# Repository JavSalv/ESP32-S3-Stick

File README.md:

# ESP32-S3 Stick

> Breadboard-friendly ESP32-S3 module with onboard RTC, LiPo battery charger, and USB-C — designed for low-power and deep-sleep applications.

---

## Overview

The ESP32-S3 Stick is a compact development module built around the **ESP32-S3-WROOM-1** that fits standard 830-point breadboards leaving room on both sides of the module.
It combines a complete power path (USB-C input, LiPo charging, and a synchronous buck converter) with an ultra-low-power RTC clock, making it well suited for prototyping battery-operated IoT nodes, data loggers, and any application that relies on deep sleep.

---

## Features

### Microcontroller
- **ESP32-S3-WROOM-1-N16R2**: Dual-core Xtensa LX7 @ up to 240 MHz, 16 MB Flash, 2 MB PSRAM
- All GPIOs broken out to the standard 22-pin headers.

### Power
- **USB-C input** (USB 2.0, 16-pin receptacle) with correct CC pull-downs for UFP/sink detection
- **MCP73831** single-cell LiPo/Li-Ion charger with 100 mA charge current (configurable via R_PROG)
- **TPS629210** synchronous buck converter for 3.3V output up to 1A.
- **P-channel MOSFET load-sharing** (DMP2045U-7) seamless switchover between USB and battery with low dropout penalty.
- **USBLC6-2SC6** TVS diode array for USB ESD protection.

### RTC
- **RV-3028-C7** — ultra-low-power RTC (40 nA), ±1 ppm accuracy, I²C interface on IO13 (SCL) / IO14 (SDA)

### Connectivity & I/O
- **USB-C** - USB 2.0 FS data lines connected directly to ESP32-S3 USB transceiver (USB_D+ / USB_D−)
- **UART0** (TXD0 / RXD0) broken out for programming and debug
- **2 × 22-pin headers** 2.54 mm pitch, breadboard-compatible

### User Interface
- **RST button**: Reset the controller
- **BOOT button**: Enters download mode when held during reset
- **3 × status LEDs**: Charge status, power status and one user LED connected to GPIO48

---

## Pin Map

The Pin Map is similar to other ESP32-S3 modules like the ESP32-S3-DevKitC-1 or cheaper AliExpress clones.

> **Note:** IO0 is the BOOT strapping pin — avoid driving it LOW at power-on unless entering download mode. IO45 and IO46 are also strapping pins; check the ESP32-S3 datasheet before using them as outputs.

### LiPo Battery

Connect a single-cell LiPo or Li-Ion battery (3.7 V nominal) to the battery connector (JST PH 2-pin 2mm pitch connector). The MCP73831 charges the battery at 100mA.

## License

Hardware design files are open source. See [LICENSE](LICENSE) for details.

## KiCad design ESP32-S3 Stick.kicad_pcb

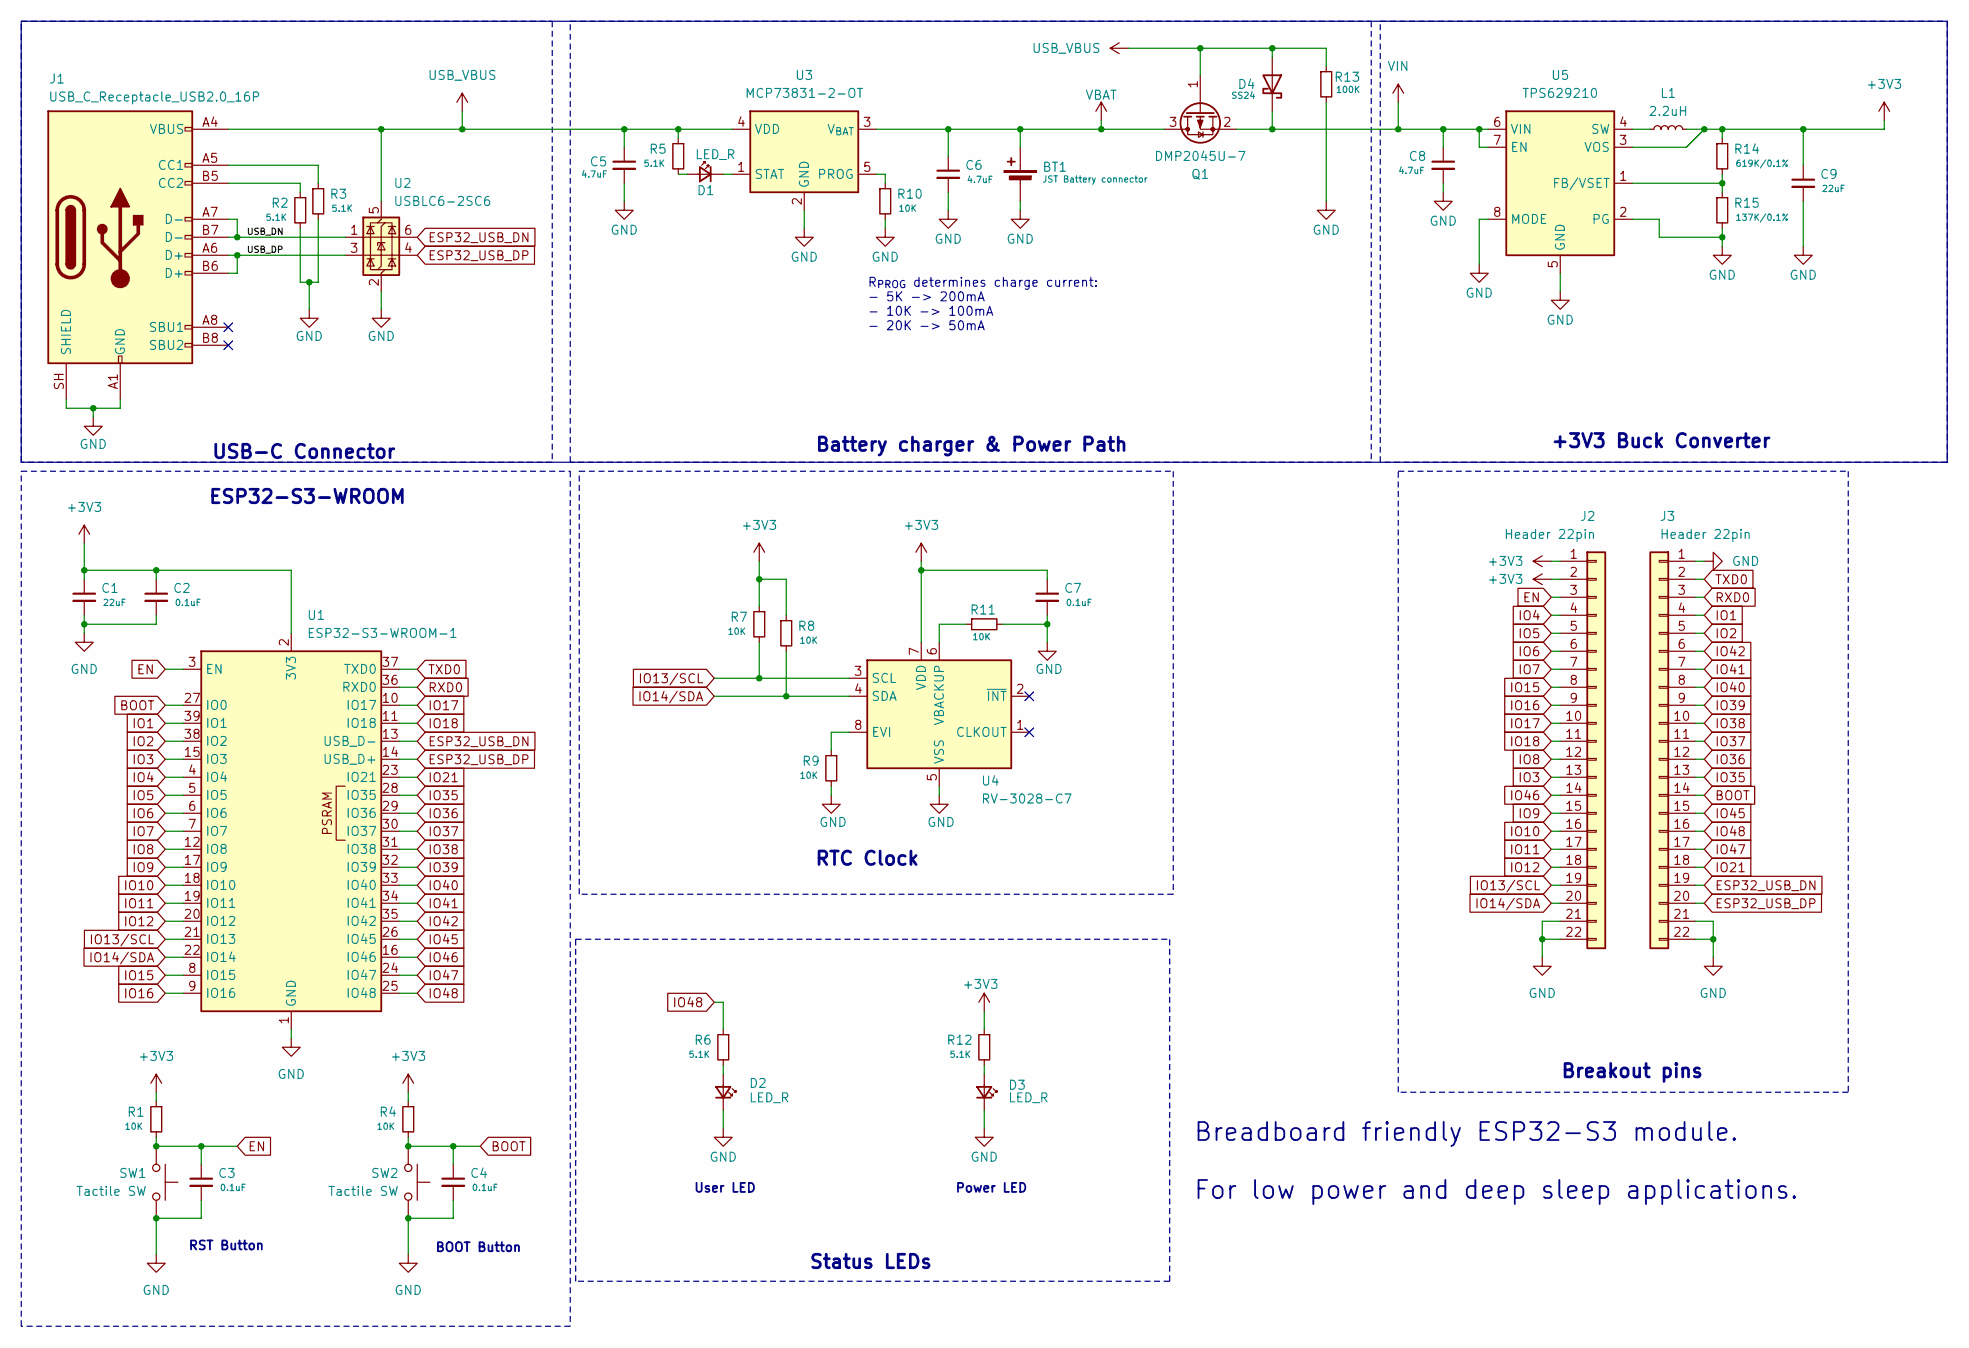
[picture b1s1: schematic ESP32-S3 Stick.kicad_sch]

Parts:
BT1: JST Battery connector; CONN-TH_B2B-PH-K-S; digikey# 455-1704-ND
C1, C9: 22uF; C_0603_1608Metric; digikey# 1276-1274-1-ND
C2, C3, C4, C7: 0.1uF; C_0603_1608Metric; digikey# 1276-1000-1-ND
C5, C6, C8: 4.7uF; C_0603_1608Metric; digikey# 1276-1900-1-ND
D1, D2, D3: LED_R; LED_0603_1608Metric; digikey# 160-1830-1-ND
D4: SS24; D_SOD-123F; digikey# 1801-SS24LWCT-ND
J1: USB_C_Receptacle_USB2.0_16P; USB_C_Receptacle_GCT_USB4105-xx-A_16P_TopMnt_Horizontal; digikey# 2073-USB4215-03-ACT-ND
J2, J3: Header 22pin; PinHeader_1x22_P2.54mm_Vertical; lcsc# C41375941
L1: 2.2uH; L_1008_2520Metric; digikey# 490-DFE252012PD-2R2M=P2CT-ND
Q1: DMP2045U-7; SOT-23; lcsc# C459541
R1, R4, R7, R8, R9, R10, R11: 10K; R_0603_1608Metric; digikey# YAG1236CT-ND
R2, R3, R5, R6, R12: 5.1K; R_0603_1608Metric; digikey# YAG1696CT-ND
R13: 100K; R_0603_1608Metric; digikey# 311-100KGRCT-ND
R14: 619K/0.1%; R_0603_1608Metric; digikey# MCT0603MD6193BP500
R15: 137K/0.1%; R_0603_1608Metric; digikey# ERA-3AEB1373V
SW1, SW2: Tactile SW; SW-SMD_L3.9-W3.0-P4.45; digikey# 4809-SKRKAEE020CT-ND
U1: ESP32-S3-WROOM-1; digikey# 5407-ESP32-S3-WROOM-1-N16R2CT-ND
U2: USBLC6-2SC6; SOT-23-6; digikey# 5399-USBLC6-2SC6CT-ND
U3: MCP73831-2-OT; SOT-23-5; digikey# MCP73831T-2ACI/OTCT-ND
U4: RV-3028-C7; MicroCrystal_C7_SON-8_1.5x3.2mm_P0.9mm; lcsc# C3019759
U5: TPS629210; SOT-583-8; digikey# 296-TPS629210DRLRCT-ND

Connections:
+3V3: C1.1, C2.1, C7.1, C9.1, J2.1, J2.2, L1.2, R1.1, R4.1, R7.1, R8.1, R12.1, R14.1, U1.2 (3V3), U4.7 (VDD), U5.3 (VOS)
/USB_DN: J1.A7 (D-), J1.B7 (D-), U2.1 (I/O1)
/USB_DP: J1.A6 (D+), J1.B6 (D+), U2.3 (I/O2)
BOOT: C4.1, J3.14, R4.2, SW2.2, U1.27 (IO0)
EN: C3.1, J2.3, R1.2, SW1.2, U1.3 (EN)
ESP32_USB_DN: J3.19, U1.13 (USB_D-), U2.6 (I/O1)
ESP32_USB_DP: J3.20, U1.14 (USB_D+), U2.4 (I/O2)
GND: BT1.2 (-), C1.2, C2.2, C3.2, C4.2, C5.2, C6.2, C7.2, C8.2, C9.2, D2.1 (K), D3.1 (K), J1.A1 (GND), J1.A12 (GND), J1.B1 (GND), J1.B12 (GND), J1.SH (SHIELD), J2.21, J2.22, J3.1, J3.21, J3.22, R2.2, R3.2, R9.2, R10.2, R11.2, R13.2, R15.2, SW1.1, SW2.1, U1.1 (GND), U1.40 (GND), U1.41 (GND), U2.2 (GND), U3.2 (GND), U4.5 (VSS), U5.2 (PG), U5.5 (GND), U5.8 (MODE)
IO1: J3.4, U1.39 (IO1)
IO2: J3.5, U1.38 (IO2)
IO3: J2.13, U1.15 (IO3)
IO4: J2.4, U1.4 (IO4)
IO5: J2.5, U1.5 (IO5)
IO6: J2.6, U1.6 (IO6)
IO7: J2.7, U1.7 (IO7)
IO8: J2.12, U1.12 (IO8)
IO9: J2.15, U1.17 (IO9)
IO10: J2.16, U1.18 (IO10)
IO11: J2.17, U1.19 (IO11)
IO12: J2.18, U1.20 (IO12)
IO13/SCL: J2.19, R7.2, U1.21 (IO13), U4.3 (SCL)
IO14/SDA: J2.20, R8.2, U1.22 (IO14), U4.4 (SDA)
IO15: J2.8, U1.8 (IO15)
IO16: J2.9, U1.9 (IO16)
IO17: J2.10, U1.10 (IO17)
IO18: J2.11, U1.11 (IO18)
IO21: J3.18, U1.23 (IO21)
IO35: J3.13, U1.28 (IO35)
IO36: J3.12, U1.29 (IO36)
IO37: J3.11, U1.30 (IO37)
IO38: J3.10, U1.31 (IO38)
IO39: J3.9, U1.32 (IO39)
IO40: J3.8, U1.33 (IO40)
IO41: J3.7, U1.34 (IO41)
IO42: J3.6, U1.35 (IO42)
IO45: J3.15, U1.26 (IO45)
IO46: J2.14, U1.16 (IO46)
IO47: J3.17, U1.24 (IO47)
IO48: J3.16, R6.1, U1.25 (IO48)
unnamed: D1.2 (A), R5.2
unnamed: D1.1 (K), U3.1 (STAT)
unnamed: D2.2 (A), R6.2
unnamed: D3.2 (A), R12.2
unnamed: J1.A5 (CC1), R3.1
unnamed: J1.B5 (CC2), R2.1
unnamed: R10.1, U3.5 (PROG)
unnamed: R9.1, U4.8 (EVI)
unnamed: R11.1, U4.6 (VBACKUP)
unnamed: R14.2, R15.1, U5.1 (FB/VSET)
unnamed: L1.1, U5.4 (SW)
RXD0: J3.3, U1.36 (RXD0)
TXD0: J3.2, U1.37 (TXD0)
USB_VBUS: C5.1, D4.2 (A), J1.A4 (VBUS), J1.A9 (VBUS), J1.B4 (VBUS), J1.B9 (VBUS), Q1.1 (G), R5.1, R13.1, U2.5 (VBUS), U3.4 (VDD)
VBAT: BT1.1 (+), C6.1, Q1.3 (D), U3.3 (V_{BAT})
VIN: C8.1, D4.1 (K), Q1.2 (S), U5.6 (VIN), U5.7 (EN)

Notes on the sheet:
BOOT Button
RTC Clock
User LED
Status LEDs
R_{PROG} determines charge current: - 5K -> 200mA - 10K -> 100mA - 20K -> 50mA
ESP32-S3-WROOM
RST Button
Breakout pins
Breadboard friendly ESP32-S3 module. For low power and deep sleep applications.
Power LED
USB-C Connector
+3V3 Buck Converter
Battery charger & Power Path

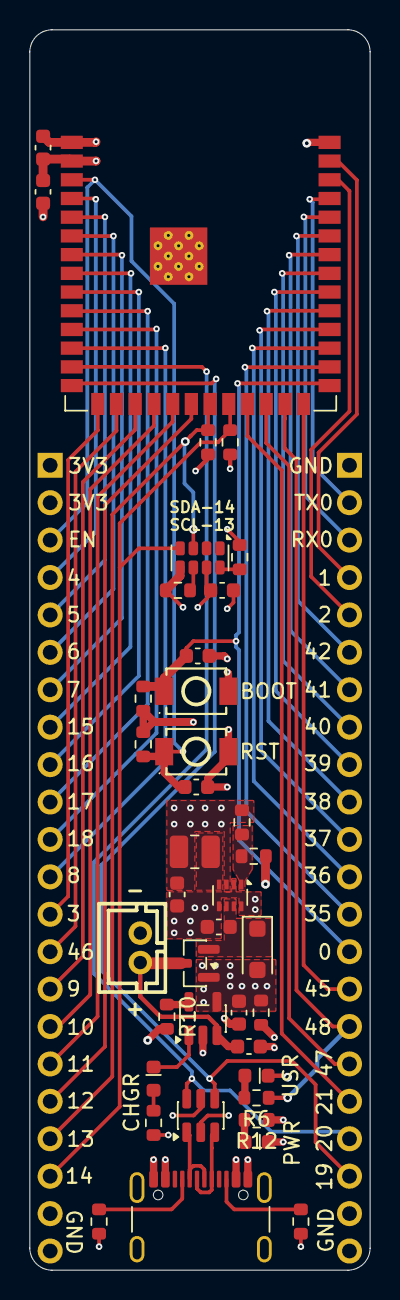
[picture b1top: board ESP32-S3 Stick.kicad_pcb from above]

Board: 4 copper layers, 23.1 x 84.2 mm, 41 parts (0 on the bottom side), 55 nets.

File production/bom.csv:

Designator,Footprint,Quantity,Value,LCSC Part #
BT1,CONN-TH_B2B-PH-K-S,1,JST Battery connector,C131337
"C1, C9",0603,2,22uF,
"C2, C3, C4, C7",0603,4,0.1uF,
"C5, C6, C8",0603,3,4.7uF,
"D1, D2, D3",0603,3,LED_R,
D4,D_SOD-123F,1,SS24,
J1,USB_C_Receptacle_GCT_USB4105-xx-A_16P_TopMnt_Horizontal,1,USB_C_Receptacle_USB2.0_16P,
"J2, J3",PinHeader_1x22_P2.54mm_Vertical,2,Header 22pin,
L1,1008,1,2.2uH,
Q1,SOT-23,1,DMP2045U-7,
"R1, R10, R11, R4, R7, R8, R9",0603,7,10K,
"R12, R2, R3, R5, R6",0603,5,5.1K,
R13,0603,1,100K,
R14,0603,1,619K/0.1%,
R15,0603,1,137K/0.1%,
"SW1, SW2",SW-SMD_L3.9-W3.0-P4.45,2,Tactile SW,C115357
U1,ESP32-S3-WROOM-1,1,ESP32-S3-WROOM-1,
U2,SOT-23-6,1,USBLC6-2SC6,
U3,SOT-23-5,1,MCP73831-2-OT,
U4,MicroCrystal_C7_SON-8_1.5x3.2mm_P0.9mm,1,RV-3028-C7,
U5,SOT-583-8,1,TPS629210,

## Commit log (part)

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2026-06-23 Add production folder
